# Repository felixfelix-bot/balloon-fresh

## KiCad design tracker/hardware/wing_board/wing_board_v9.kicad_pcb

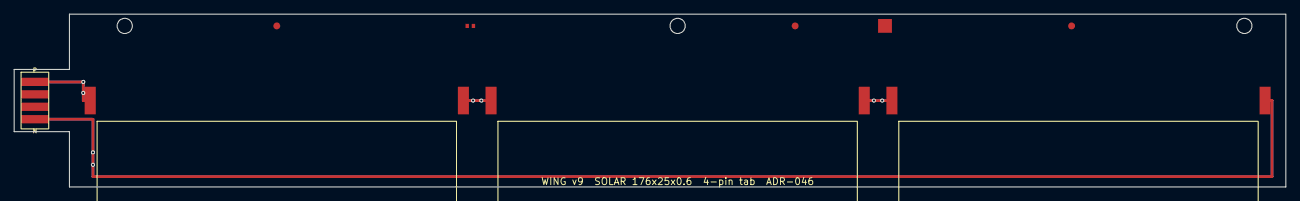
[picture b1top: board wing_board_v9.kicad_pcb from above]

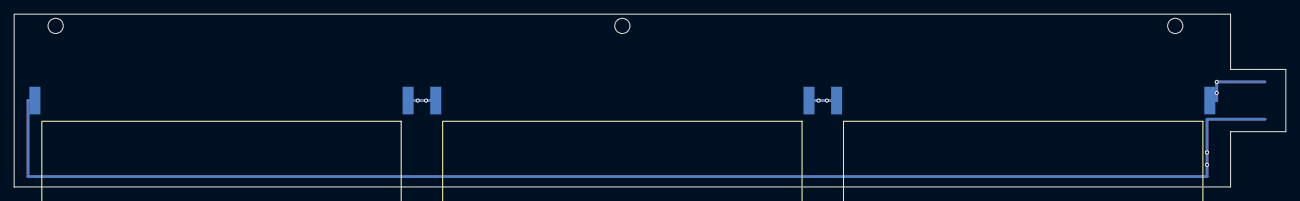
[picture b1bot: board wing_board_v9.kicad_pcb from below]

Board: 2 copper layers, 184.0 x 25.0 mm, 15 parts (3 on the bottom side), 4 nets.

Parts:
FB1: FerriteBead_0402_DNP_V2only; FerriteBead_0402_V2provision
FID1, FID2, FID3: Fiducial_1mm_Mask2mm
H1, H2, H3: MountingHole_NPTH_2.2mm; MountingHole_2.2mm_NPTH
J1: WingTab_v9_4pin
RF1: RF_ProvisionPad_v2only
SC1, SC2, SC3, SC4, SC5, SC6: SolarCell_52x19mm_0.5V; SolarCell_52x19mm

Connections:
SOLAR_MID1: SC1.2, SC2.1, SC4.2, SC5.1
SOLAR_MID2: SC2.2, SC3.1, SC5.2, SC6.1
SOLAR_N: J1.4, SC3.2, SC6.2
SOLAR_P: J1.1, SC1.1, SC4.1
